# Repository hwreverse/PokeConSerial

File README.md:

# PokeConSerial
Serial Interfaces for Pocket Computers (ポケコン) (Sharp, Casio, TRS80-M100,...)<br>
(PCB Layouts are in KiCAD 5.1.6*)

- <a href="g850_kiss/">Sharp G800/G850/V/S/VS 11pin USB to Serial Interface</a>

- <a href="Sharp_11pin_to_15pin_Adapter/">Sharp 11pin to 15pin Adapter</a>
  (to use the Sharp G850* USB to Serial adapter with the Sharp PC-E500 and the Sharp PC-1600)

- <a href="PC1600SIO/">Sharp PC-E500 / PC-1600 15pin USB to Serial Interface</a>

- Casio FA-7 compatible (for PB-1000, AI-1000, PB-2000C) USB Interface (soon, needs to be validated)

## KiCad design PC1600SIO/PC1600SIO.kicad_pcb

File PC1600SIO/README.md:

# SHARP PC-E500/E500S/PC-1600/PC-1600K 15pin USB to Serial Interface
USB to Serial (FT232RL based) Interface for the SHARP PC-E500 / E500S / PC-1600 / PC-1600K line of Pocket Computers 

## Important
NB 1: the 15pin adapter is a 1x15 pin 1.27mm (50mil) male connector<br>
NB 2: You have to bridge the right solderjumper (RR or RTS) depending on the mode you use for it to work. I have RTS bridged usually 

## Components

The USB-B-micro Receptacle in this schema is a Molex 105017-0001 / 105017-1001, every LED / R / L / C is 0805, FT232RL is a SSOP28, the Polyfuse is a 1210 PTC Resettable fuse, 500-700mA or similar

## After-Construction Configuration

As the Sharp Pocket computers use <b>inverted</b> Levels, you have to invert RXD, TXD, RTS# and CTS# on your FT232RL chip too.

You do this by downloading the program <b>FTProg</b> from the FTDI Site :  <a href="https://www.ftdichip.com/Support/Utilities.htm#FT_PROG">Here</a>.

You need also to configure CBUS0 as RXLED and CBUS1 as TXLED in order to gain LED Functionality.

<b> AND FOR HEAVEANS' SAKE:</b> Never set the FT chip to External OSC (Escpecially on this board where it does not have an External Oscillator) lest you are self-destructive and want to brick your chip !

-------------------------

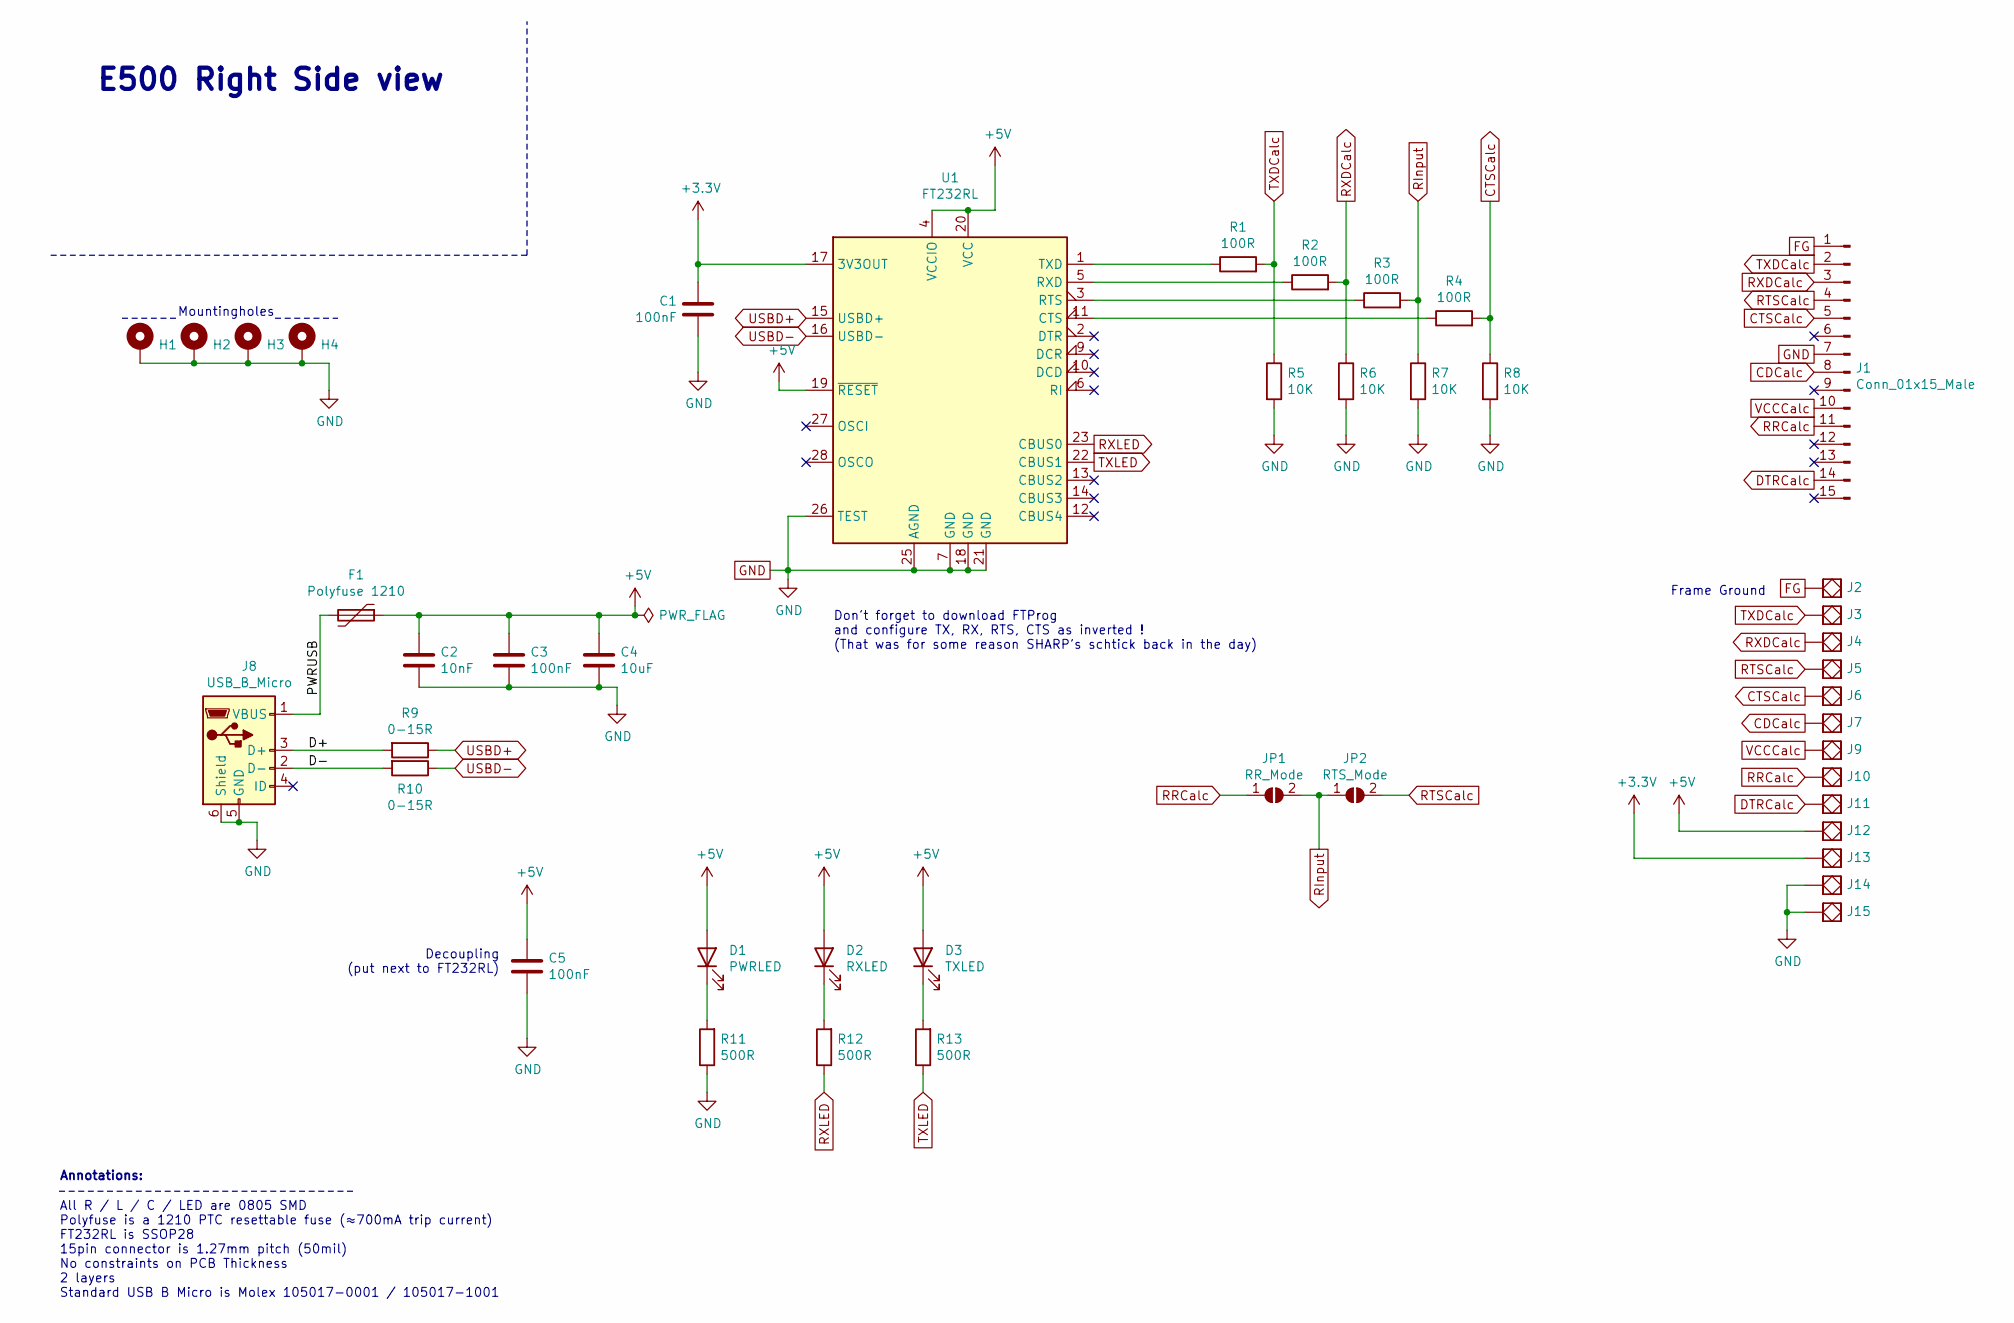
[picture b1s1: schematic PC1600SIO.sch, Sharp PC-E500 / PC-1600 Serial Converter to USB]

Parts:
C1, C3, C5: 100nF; C_0805_2012Metric_Pad1.15x1.40mm_HandSolder
C2: 10nF; C_0805_2012Metric_Pad1.15x1.40mm_HandSolder
C4: 10uF; C_0805_2012Metric_Pad1.15x1.40mm_HandSolder
D1: PWRLED; LED_0805_2012Metric_Pad1.15x1.40mm_HandSolder
D2: RXLED; LED_0805_2012Metric_Pad1.15x1.40mm_HandSolder
D3: TXLED; LED_0805_2012Metric_Pad1.15x1.40mm_HandSolder
F1: Polyfuse 1210; R_1210_3225Metric_Pad1.42x2.65mm_HandSolder
H1, H2, H3, H4: MountingHole_Pad; MountingHole_2.5mm_Pad
J1: Conn_01x15_Male; PinHeader_1x15_P1.27mm_Vertical
J2, J3, J4, J5, J6, J7, J9, J10, J11, J12, J13, J14, J15: SolidPad-Connector; SolidPad_4x4mm_2x2mmCore
J8: USB_B_Micro; USB_Micro-B_Molex-105017-0001
JP1: RR_Mode; SolderJumper-2_P1.3mm_Open_RoundedPad1.0x1.5mm
JP2: RTS_Mode; SolderJumper-2_P1.3mm_Open_RoundedPad1.0x1.5mm
R1, R2, R3, R4: 100R; R_0805_2012Metric_Pad1.15x1.40mm_HandSolder
R5, R6, R7, R8: 10K; R_0805_2012Metric_Pad1.15x1.40mm_HandSolder
R9, R10: 0-15R; R_0805_2012Metric_Pad1.15x1.40mm_HandSolder
R11, R12, R13: 500R; R_0805_2012Metric_Pad1.15x1.40mm_HandSolder
U1: FT232RL; SSOP-28_5.3x10.2mm_P0.65mm

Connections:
+3V3: C1.1, J13.~, U1.17 (3V3OUT)
+5V: C2.1, C3.1, C4.1, C5.1, D1.2 (A), D2.2 (A), D3.2 (A), F1.1, J12.~, U1.4 (VCCIO), U1.19 (~RESET~), U1.20 (VCC)
/D+: J8.3 (D+), R9.2
/D-: J8.2 (D-), R10.2
/PWRUSB: F1.2, J8.1 (VBUS)
CDCalc: J1.8, J7.~
CTSCalc: J1.5, J6.~, R4.2, R8.1
DTRCalc: J1.14, J11.~
FG: J1.1, J2.~
GND: C1.2, C2.2, C3.2, C4.2, C5.2, H1.1, H2.1, H3.1, H4.1, J1.7, J8.5 (GND), J8.6 (Shield), J14.~, J15.~, R5.2, R6.2, R7.2, R8.2, R11.1, U1.7 (GND), U1.18 (GND), U1.21 (GND), U1.25 (AGND), U1.26 (TEST)
unnamed: D1.1 (K), R11.2
unnamed: D2.1 (K), R12.2
unnamed: D3.1 (K), R13.2
unnamed: R1.1, U1.1 (TXD)
unnamed: R2.1, U1.5 (RXD)
unnamed: R3.1, U1.3 (RTS)
unnamed: R4.1, U1.11 (CTS)
RInput: JP1.2 (B), JP2.1 (A), R3.2, R7.1
RRCalc: J1.11, J10.~, JP1.1 (A)
RTSCalc: J1.4, J5.~, JP2.2 (B)
RXDCalc: J1.3, J4.~, R2.2, R6.1
RXLED: R12.1, U1.23 (CBUS0)
TXDCalc: J1.2, J3.~, R1.2, R5.1
TXLED: R13.1, U1.22 (CBUS1)
USBD+: R9.1, U1.15 (USBD+)
USBD-: R10.1, U1.16 (USBD-)
VCCCalc: J1.10, J9.~

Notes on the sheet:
E500 Right Side view
Mountingholes
All R / L / C / LED are 0805 SMD Polyfuse is a 1210 PTC resettable fuse (≈700mA trip current) FT232RL is SSOP28 15pin connector is 1.27mm pitch (50mil) No constraints on PCB Thickness 2 layers Standard USB B Micro is Molex 105017-0001 / 105017-1001
Annotations:
Decoupling (put next to FT232RL)
Frame Ground
Don't forget to download FTProg and configure TX, RX, RTS, CTS as inverted ! (That was for some reason SHARP's schtick back in the day)

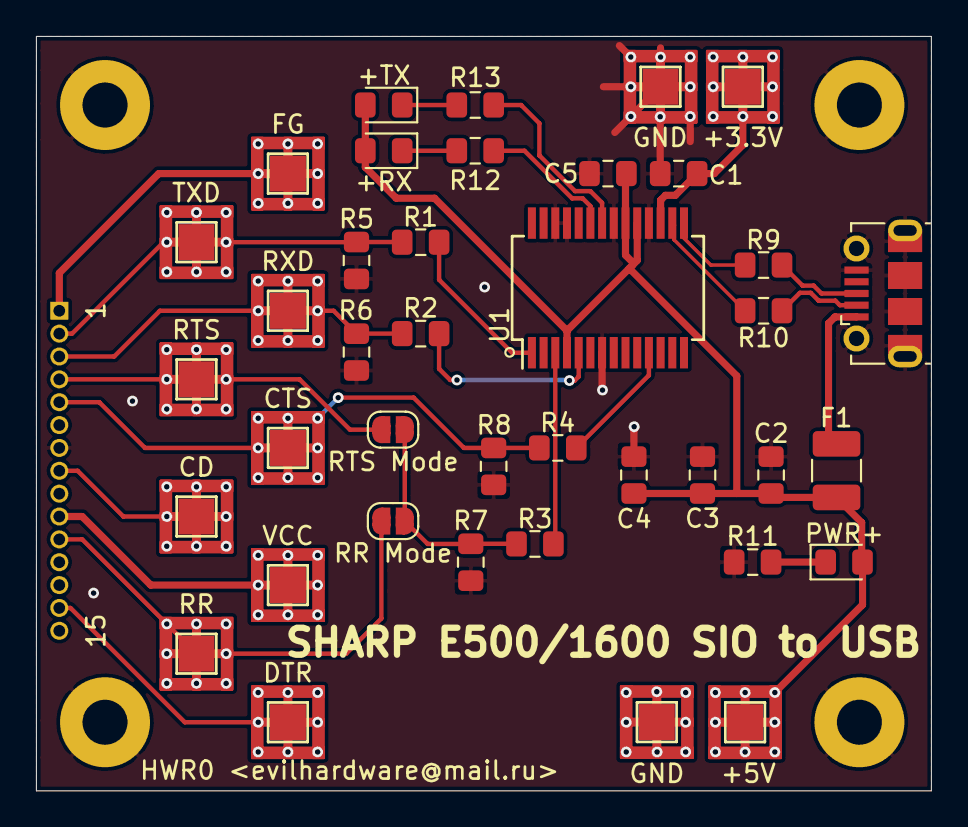
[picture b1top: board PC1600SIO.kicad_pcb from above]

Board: 2 copper layers, 49.7 x 41.9 mm, 44 parts (0 on the bottom side), 27 nets.

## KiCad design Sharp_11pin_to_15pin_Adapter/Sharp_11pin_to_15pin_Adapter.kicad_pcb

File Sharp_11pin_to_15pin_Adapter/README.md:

# SHARP 11pin to 15pin Adapter
Adapter to use with the <a href="https://github.com/hwreverse/PokeConSerial/tree/master/g850_kiss">Sharp G800* USB to Serial Interface</a>
to make it work for the SHARP PC-E500 and the Sharp PC-1600

NB 1: the 11pin adapter is a 1x11 pin 2.54mm (100mil) female connector, the 15pin adaptor is a 1x15pin 1.27mm (50mil) male connector

NB 2: You have to bridge the right solderjumper (RR or RTS) depending on the mode you use for it to work. I use RTS with both calculators

NB 3: Use VCC Connect if for some reason, you want to power the device from USB (use with *EXTREME* care!!)

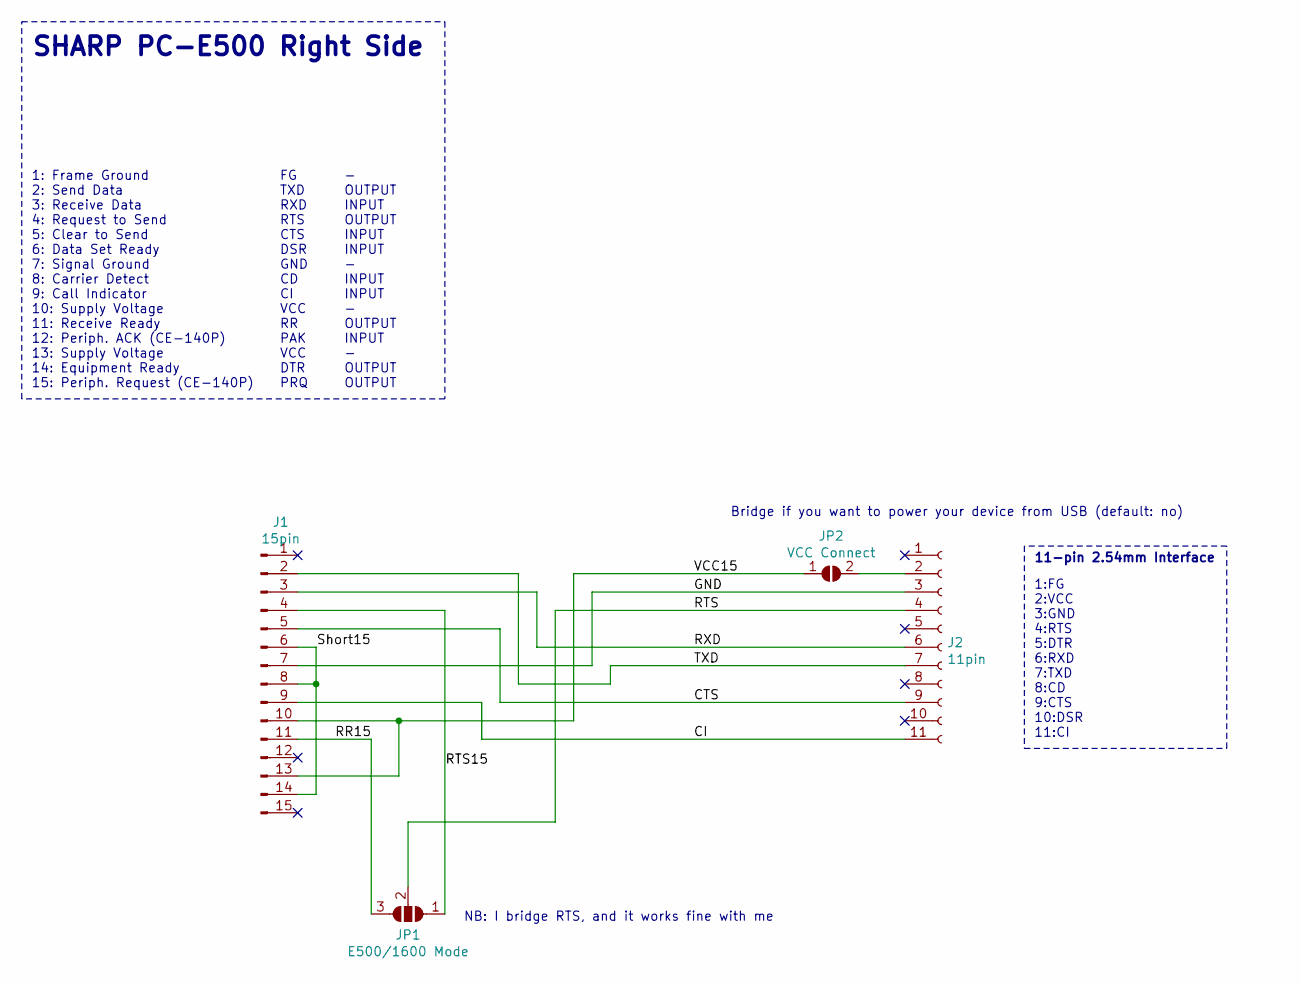
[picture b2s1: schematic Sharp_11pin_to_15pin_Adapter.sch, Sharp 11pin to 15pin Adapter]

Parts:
J1: 15pin; PinHeader_1x15_P1.27mm_Horizontal_mirror
J2: 11pin; PinSocket_1x11_P2.54mm_Horizontal-mirror
JP1: E500/1600 Mode; SolderJumper-3_P1.3mm_Open_RoundedPad1.0x1.5mm
JP2: VCC Connect; SolderJumper-2_P1.3mm_Open_RoundedPad1.0x1.5mm

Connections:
/CI: J1.9, J2.11
/CTS: J1.5, J2.9
/GND: J1.7, J2.3
/RR15: J1.11, JP1.3 (B)
/RTS: J2.4, JP1.2 (C)
/RTS15: J1.4, JP1.1 (A)
/RXD: J1.3, J2.6
/Short15: J1.6, J1.8, J1.14
/TXD: J1.2, J2.7
/VCC15: J1.10, J1.13, JP2.1 (A)
unnamed: J2.2, JP2.2 (B)

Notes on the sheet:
1:FG 2:VCC 3:GND 4:RTS 5:DTR 6:RXD 7:TXD 8:CD 9:CTS 10:DSR 11:CI
11-pin 2.54mm Interface
1: Frame Ground 2: Send Data 3: Receive Data 4: Request to Send 5: Clear to Send 6: Data Set Ready 7: Signal Ground 8: Carrier Detect 9: Call Indicator 10: Supply Voltage 11: Receive Ready 12: Periph. ACK (CE-140P) 13: Supply Voltage 14: Equipment Ready 15: Periph. Request (CE-140P)
FG TXD RXD RTS CTS DSR GND CD CI VCC RR PAK VCC DTR PRQ
- OUTPUT INPUT OUTPUT INPUT INPUT - INPUT INPUT - OUTPUT INPUT - OUTPUT OUTPUT
SHARP PC-E500 Right Side
NB: I bridge RTS, and it works fine with me
Bridge if you want to power your device from USB (default: no)

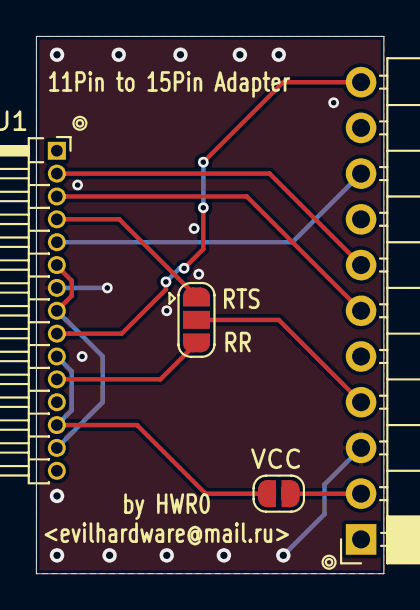
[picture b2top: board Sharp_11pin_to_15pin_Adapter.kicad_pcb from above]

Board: 2 copper layers, 19.3 x 29.8 mm, 4 parts (0 on the bottom side), 11 nets.

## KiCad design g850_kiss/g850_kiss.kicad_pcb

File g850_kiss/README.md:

# SHARP PC-G800*/G850*/V/S/VS 11pin USB to Serial Interface
USB to Serial (FT232RL based) Interface for the SHARP G800* line of Pocket Computers (G811, G850, G850V, G850S, G850VS)

## Important
NB1: the 11pin adapter is a 1x11 pin 2.54mm (100mil) male connector<br>
NB2: Use VCC Connect if for some reason, you want to power the device from USB (use with *EXTREME* care!!)<br>
NB3: Bridge the 5V VCCIO Solder Jumper to work with the G850*, this sets the I/O Level to 5V<br>

## Components

The USB-B-micro Receptacle in this schema is a Molex 105017-0001 / 105017-1001, every diode / R / C is 0805, FT232RL is a SSOP28, the Polyfuse is a 1210 500mA or similar

## After-Construction Configuration

As the Sharp Pocket computers use <b>inverted</b> Levels, you have to invert RXD, TXD, RTS# and CTS# on your FT232RL chip too.

You do this by downloading the program <b>FTProg</b> from the FTDI Site :  <a href="https://www.ftdichip.com/Support/Utilities.htm#FT_PROG">Here</a>.

You need also to configure CBUS0 as RXLED and CBUS1 as TXLED in order to gain LED Functionality.

<b> AND FOR HEAVENS' SAKE:</b> Never set the FT chip to External OSC (Escpecially on this board where it does not have an External Oscillator) lest you are self-destructive and want to brick your chip !

-------------------------

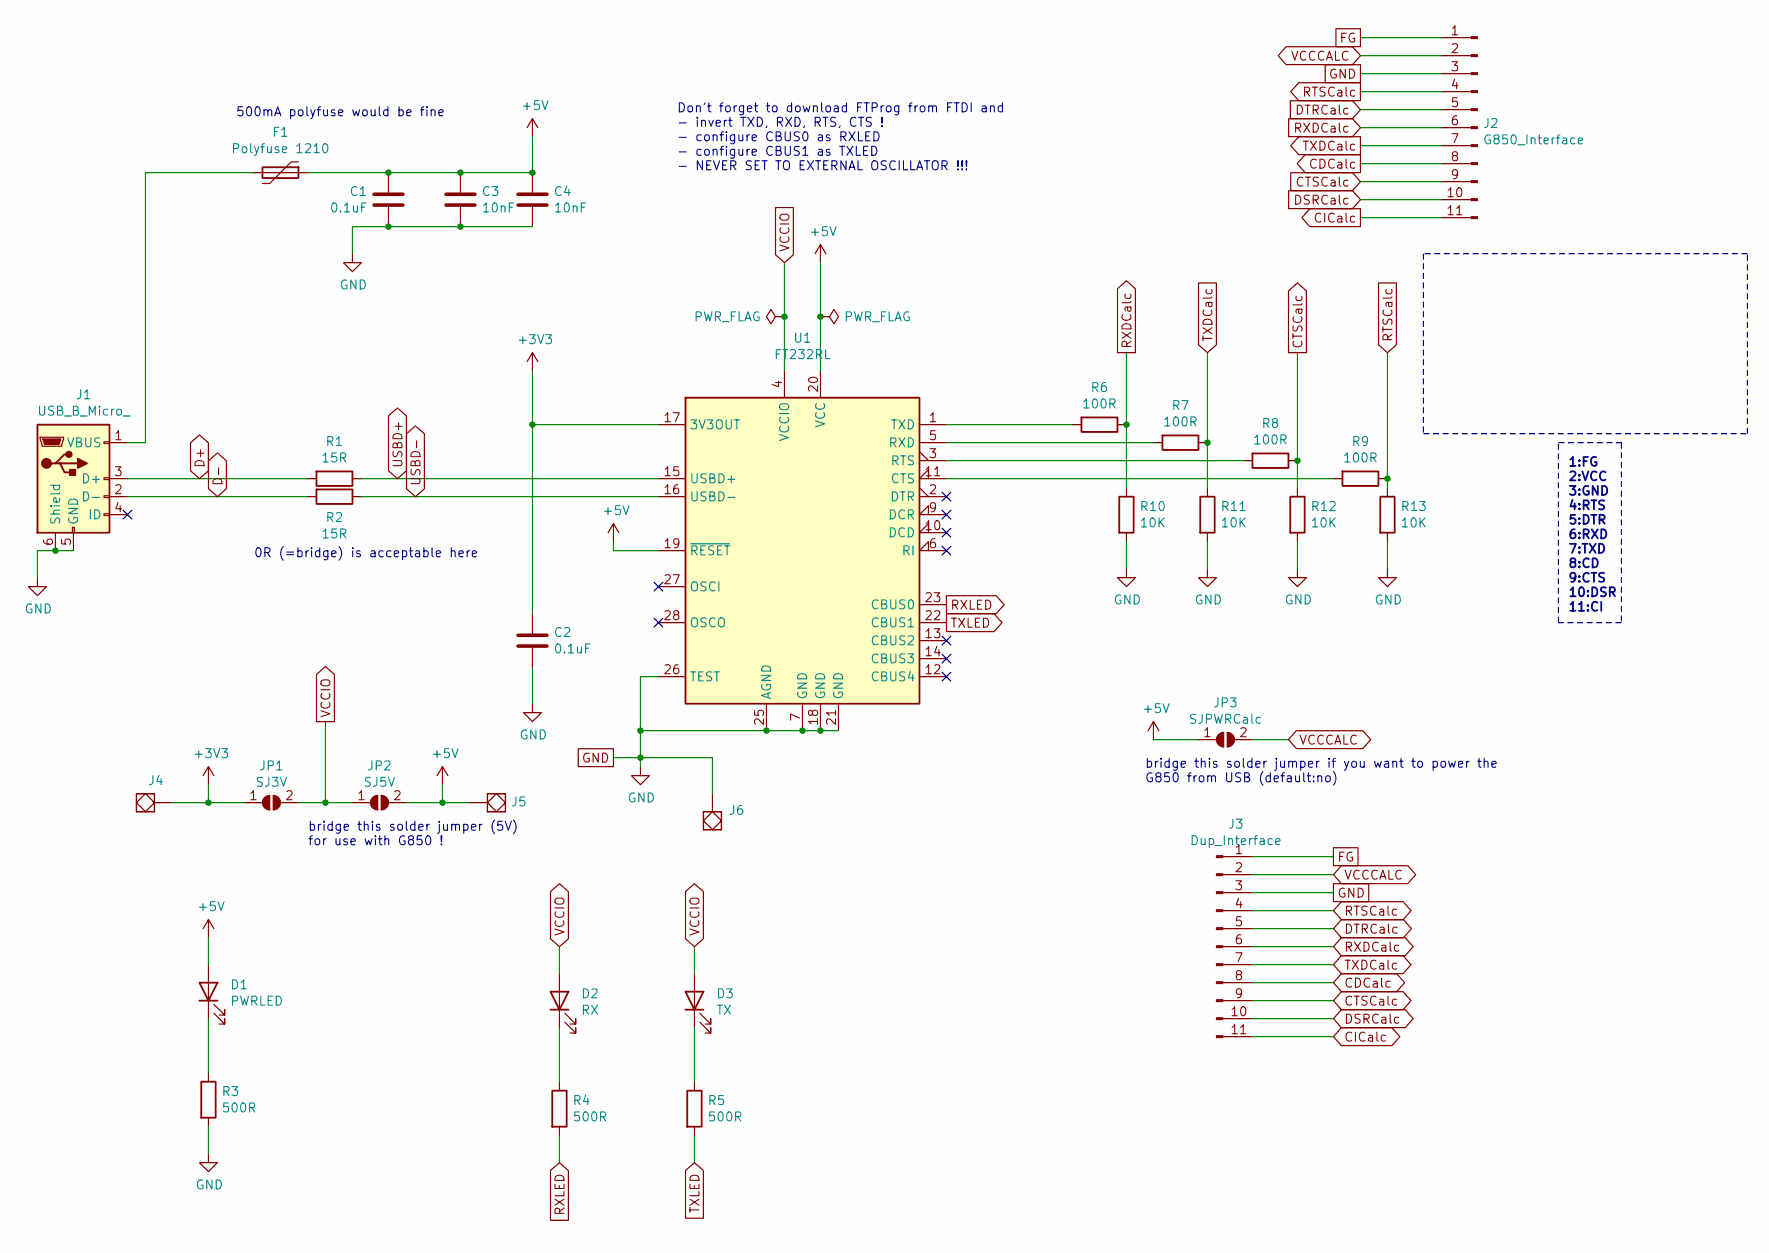
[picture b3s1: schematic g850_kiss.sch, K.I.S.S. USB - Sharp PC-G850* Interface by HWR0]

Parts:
C1, C2: 0.1uF; C_0805_2012Metric_Pad1.15x1.40mm_HandSolder
C3, C4: 10nF; C_0805_2012Metric_Pad1.15x1.40mm_HandSolder
D1: PWRLED; LED_0805_2012Metric_Pad1.15x1.40mm_HandSolder
D2: RX; LED_0805_2012Metric_Pad1.15x1.40mm_HandSolder
D3: TX; LED_0805_2012Metric_Pad1.15x1.40mm_HandSolder
F1: Polyfuse 1210; R_1210_3225Metric_Pad1.42x2.65mm_HandSolder
J1: USB_B_Micro_; USB_Micro-B_Molex-105017-0001
J2: G850_Interface; PinHeader_1x11_P2.54mm_Horizontal
J3: Dup_Interface; PinHeader_1x11_P2.54mm_Vertical
J4, J5, J6: SolidPad-Connector; SolidPad_4x4mm_2x2mmCore
JP1: SJ3V; SolderJumper-2_P1.3mm_Open_RoundedPad1.0x1.5mm
JP2: SJ5V; SolderJumper-2_P1.3mm_Open_RoundedPad1.0x1.5mm
JP3: SJPWRCalc; SolderJumper-2_P1.3mm_Open_RoundedPad1.0x1.5mm
R1, R2: 15R; R_0805_2012Metric_Pad1.15x1.40mm_HandSolder
R3, R4, R5: 500R; R_0805_2012Metric_Pad1.15x1.40mm_HandSolder
R6, R7, R8, R9: 100R; R_0805_2012Metric_Pad1.15x1.40mm_HandSolder
R10, R11, R12, R13: 10K; R_0805_2012Metric_Pad1.15x1.40mm_HandSolder
U1: FT232RL; SSOP-28_5.3x10.2mm_P0.65mm

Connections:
+3V3: C2.1, J4.~, JP1.1 (A), U1.17 (3V3OUT)
+5V: C1.1, C3.1, C4.1, D1.2 (A), F1.1, J5.~, JP2.2 (B), JP3.1 (A), U1.19 (~RESET~), U1.20 (VCC)
CDCalc: J2.8, J3.8
CICalc: J2.11, J3.11
CTSCalc: J2.9, J3.9, R8.1, R12.1
D+: J1.3 (D+), R1.2
D-: J1.2 (D-), R2.2
DSRCalc: J2.10, J3.10
DTRCalc: J2.5, J3.5
FG: J2.1, J3.1
GND: C1.2, C2.2, C3.2, C4.2, J1.5 (GND), J1.6 (Shield), J2.3, J3.3, J6.~, R3.2, R10.2, R11.2, R12.2, R13.2, U1.7 (GND), U1.18 (GND), U1.21 (GND), U1.25 (AGND), U1.26 (TEST)
unnamed: D1.1 (K), R3.1
unnamed: D2.1 (K), R4.1
unnamed: D3.1 (K), R5.1
unnamed: F1.2, J1.1 (VBUS)
unnamed: R6.2, U1.1 (TXD)
unnamed: R7.2, U1.5 (RXD)
unnamed: R8.2, U1.3 (RTS)
unnamed: R9.2, U1.11 (CTS)
RTSCalc: J2.4, J3.4, R9.1, R13.1
RXDCalc: J2.6, J3.6, R6.1, R10.1
RXLED: R4.2, U1.23 (CBUS0)
TXDCalc: J2.7, J3.7, R7.1, R11.1
TXLED: R5.2, U1.22 (CBUS1)
USBD+: R1.1, U1.15 (USBD+)
USBD-: R2.1, U1.16 (USBD-)
VCCCALC: J2.2, J3.2, JP3.2 (B)
VCCIO: D2.2 (A), D3.2 (A), JP1.2 (B), JP2.1 (A), U1.4 (VCCIO)

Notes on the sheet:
1:FG 2:VCC 3:GND 4:RTS 5:DTR 6:RXD 7:TXD 8:CD 9:CTS 10:DSR 11:CI
bridge this solder jumper if you want to power the G850 from USB (default:no)
bridge this solder jumper (5V) for use with G850 !
500mA polyfuse would be fine
0R (=bridge) is acceptable here
Don't forget to download FTProg from FTDI and - invert TXD, RXD, RTS, CTS ! - configure CBUS0 as RXLED - configure CBUS1 as TXLED - NEVER SET TO EXTERNAL OSCILLATOR !!!

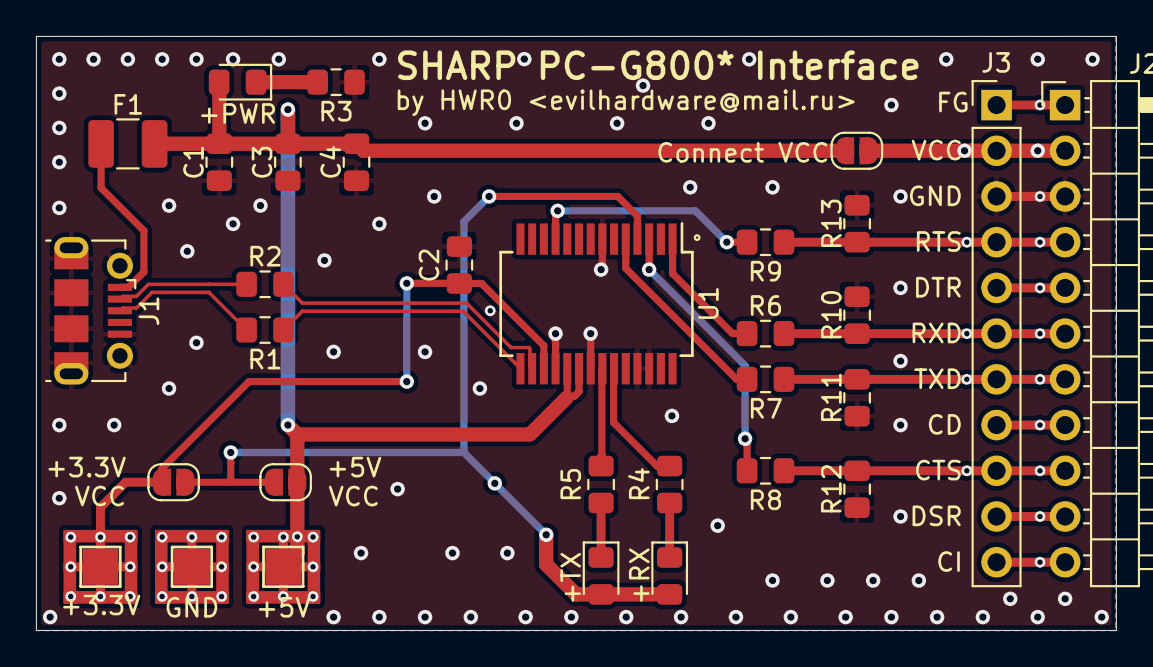
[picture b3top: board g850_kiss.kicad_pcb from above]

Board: 2 copper layers, 60.0 x 33.0 mm, 31 parts (0 on the bottom side), 28 nets.

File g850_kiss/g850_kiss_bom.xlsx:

Source: | O:\elec\g850_kiss\g850_kiss.sch
Date: | 43827.644074074073
Tool: | Eeschema (5.1.5)-3
Component Count: | 28
Ref | Value | Footprint | Datasheet | Manufacturer | Vendor
C1 | 0.1uF | Capacitor_SMD:C_0805_2012Metric_Pad1.15x1.40mm_HandSolder | ~
C2 | 0.1uF | Capacitor_SMD:C_0805_2012Metric_Pad1.15x1.40mm_HandSolder | ~
C3 | 10nF | Capacitor_SMD:C_0805_2012Metric_Pad1.15x1.40mm_HandSolder | ~
C4 | 10nF | Capacitor_SMD:C_0805_2012Metric_Pad1.15x1.40mm_HandSolder | ~
D1 | PWRLED | LED_SMD:LED_0805_2012Metric_Pad1.15x1.40mm_HandSolder | ~
D2 | RX | LED_SMD:LED_0805_2012Metric_Pad1.15x1.40mm_HandSolder | ~
D3 | TX | LED_SMD:LED_0805_2012Metric_Pad1.15x1.40mm_HandSolder | ~
F1 | Polyfuse 1210 | Resistor_SMD:R_1210_3225Metric_Pad1.42x2.65mm_HandSolder | 500mA polyfuse (1210)
J1 | USB_B_Micro | hwreverse:USB_Micro-B_Molex-105017-0001 | Molex-105017-0001 USB micro
J2 | G850_Input_Connector | Connector_PinHeader_2.54mm:PinHeader_1x11_P2.54mm_Horizontal | ~
J3 | Dup_G850_Connector | Connector_PinHeader_2.54mm:PinHeader_1x11_P2.54mm_Vertical | ~
JP1 | SJ3V | Jumper:SolderJumper-2_P1.3mm_Open_RoundedPad1.0x1.5mm | ~
JP2 | SJ5V | Jumper:SolderJumper-2_P1.3mm_Open_RoundedPad1.0x1.5mm | ~
JP3 | SJPWRCalc | Jumper:SolderJumper-2_P1.3mm_Open_RoundedPad1.0x1.5mm | ~
R1 | 15R | Resistor_SMD:R_0805_2012Metric_Pad1.15x1.40mm_HandSolder | ~
R2 | 15R | Resistor_SMD:R_0805_2012Metric_Pad1.15x1.40mm_HandSolder | ~
R3 | 500R | Resistor_SMD:R_0805_2012Metric_Pad1.15x1.40mm_HandSolder | ~
R4 | 500R | Resistor_SMD:R_0805_2012Metric_Pad1.15x1.40mm_HandSolder | ~
R5 | 500R | Resistor_SMD:R_0805_2012Metric_Pad1.15x1.40mm_HandSolder | ~
R6 | 100R | Resistor_SMD:R_0805_2012Metric_Pad1.15x1.40mm_HandSolder | ~
R7 | 100R | Resistor_SMD:R_0805_2012Metric_Pad1.15x1.40mm_HandSolder | ~
R8 | 100R | Resistor_SMD:R_0805_2012Metric_Pad1.15x1.40mm_HandSolder | ~
R9 | 100R | Resistor_SMD:R_0805_2012Metric_Pad1.15x1.40mm_HandSolder | ~
R10 | 10K | Resistor_SMD:R_0805_2012Metric_Pad1.15x1.40mm_HandSolder | ~
R11 | 10K | Resistor_SMD:R_0805_2012Metric_Pad1.15x1.40mm_HandSolder | ~
R12 | 10K | Resistor_SMD:R_0805_2012Metric_Pad1.15x1.40mm_HandSolder | ~
R13 | 10K | Resistor_SMD:R_0805_2012Metric_Pad1.15x1.40mm_HandSolder | ~
U1 | FT232RL | Package_SO:SSOP-28_5.3x10.2mm_P0.65mm | https://www.ftdichip.com/Support/Documents/DataSheets/ICs/DS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

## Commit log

2020-08-10 First Commit
    upload of G850 K.I.S.S. Interface and 11 to 15pin adapter
2020-08-10 img change
2020-08-10 updated pngs in img
2020-08-10 Create Readme in 11to15
2020-08-10 img folders
2020-08-10 ftprog
2020-08-10 Readme in g850
2020-08-10 smaller ftprog
2020-08-24 Added E500/PC-1600 USB to Serial Adapter
